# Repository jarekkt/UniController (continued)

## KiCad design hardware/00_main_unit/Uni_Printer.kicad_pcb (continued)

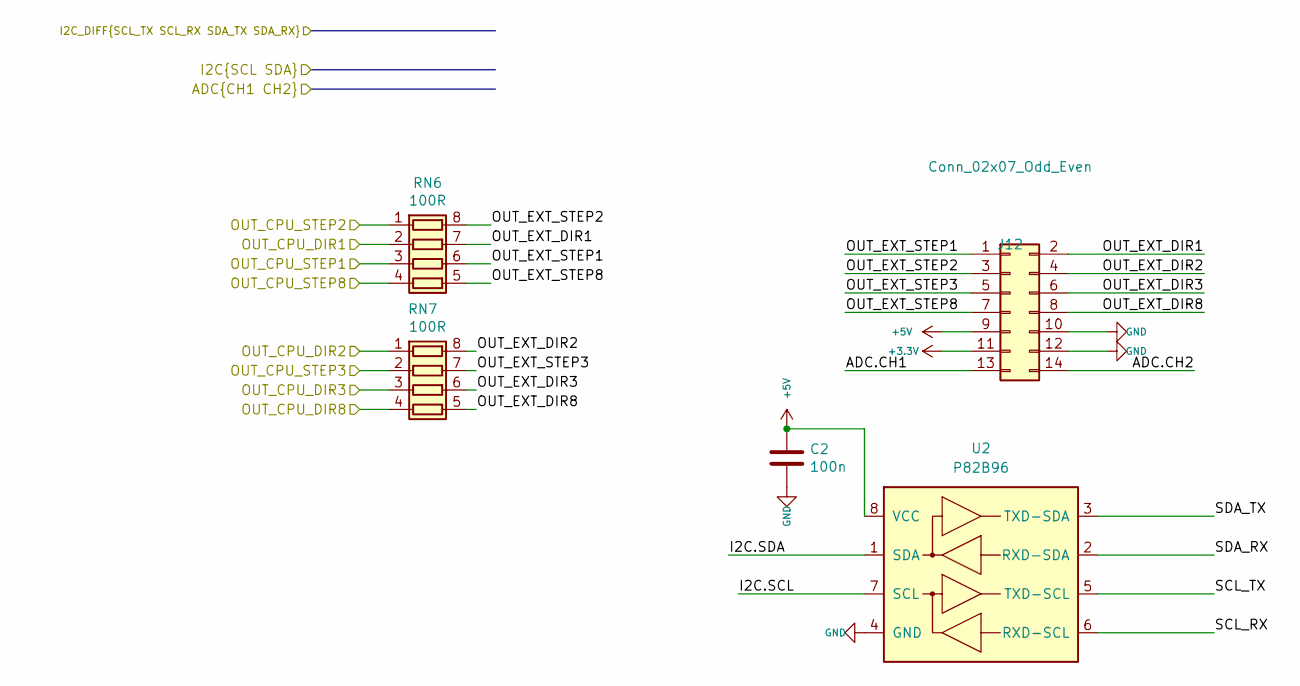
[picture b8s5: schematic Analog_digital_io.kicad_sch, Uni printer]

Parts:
C2: 100n; C_0603_1608Metric
J12: Conn_02x07_Odd_Even; PinHeader_2x07_P2.54mm_Vertical
RN6, RN7: 100R; R_Array_Convex_4x0603
U2: P82B96; TSSOP-8_4.4x3mm_P0.65mm

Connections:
+5V: C2.1, J12.9, U2.8 (VCC); also elsewhere on the board
/ADC.CH1: J12.13; also elsewhere on the board
/ADC.CH2: J12.14; also elsewhere on the board
/Analog Digital IO/OUT_EXT_DIR1: J12.2, RN6.7 (R2.2)
/Analog Digital IO/OUT_EXT_DIR2: J12.4, RN7.8 (R1.2)
/Analog Digital IO/OUT_EXT_DIR3: J12.6, RN7.6 (R3.2)
/Analog Digital IO/OUT_EXT_DIR8: J12.8, RN7.5 (R4.2)
/Analog Digital IO/OUT_EXT_STEP1: J12.1, RN6.6 (R3.2)
/Analog Digital IO/OUT_EXT_STEP2: J12.3, RN6.8 (R1.2)
/Analog Digital IO/OUT_EXT_STEP3: J12.5, RN7.7 (R2.2)
/Analog Digital IO/OUT_EXT_STEP8: J12.7, RN6.5 (R4.2)
/Analog Digital IO/SCL_RX: U2.6 (RXD-SCL)
/Analog Digital IO/SCL_TX: U2.5 (TXD-SCL)
/Analog Digital IO/SDA_RX: U2.2 (RXD-SDA)
/Analog Digital IO/SDA_TX: U2.3 (TXD-SDA)
/I2C.SCL: U2.7 (SCL); also elsewhere on the board
/I2C.SDA: U2.1 (SDA); also elsewhere on the board
/OUT_DIR1: RN6.2 (R2.1); also elsewhere on the board
/OUT_DIR2: RN7.1 (R1.1); also elsewhere on the board
/OUT_DIR3: RN7.3 (R3.1); also elsewhere on the board
/OUT_DIR8: RN7.4 (R4.1); also elsewhere on the board
/OUT_STEP1: RN6.3 (R3.1); also elsewhere on the board
/OUT_STEP2: RN6.1 (R1.1); also elsewhere on the board
/OUT_STEP3: RN7.2 (R2.1); also elsewhere on the board
/OUT_STEP8: RN6.4 (R4.1); also elsewhere on the board

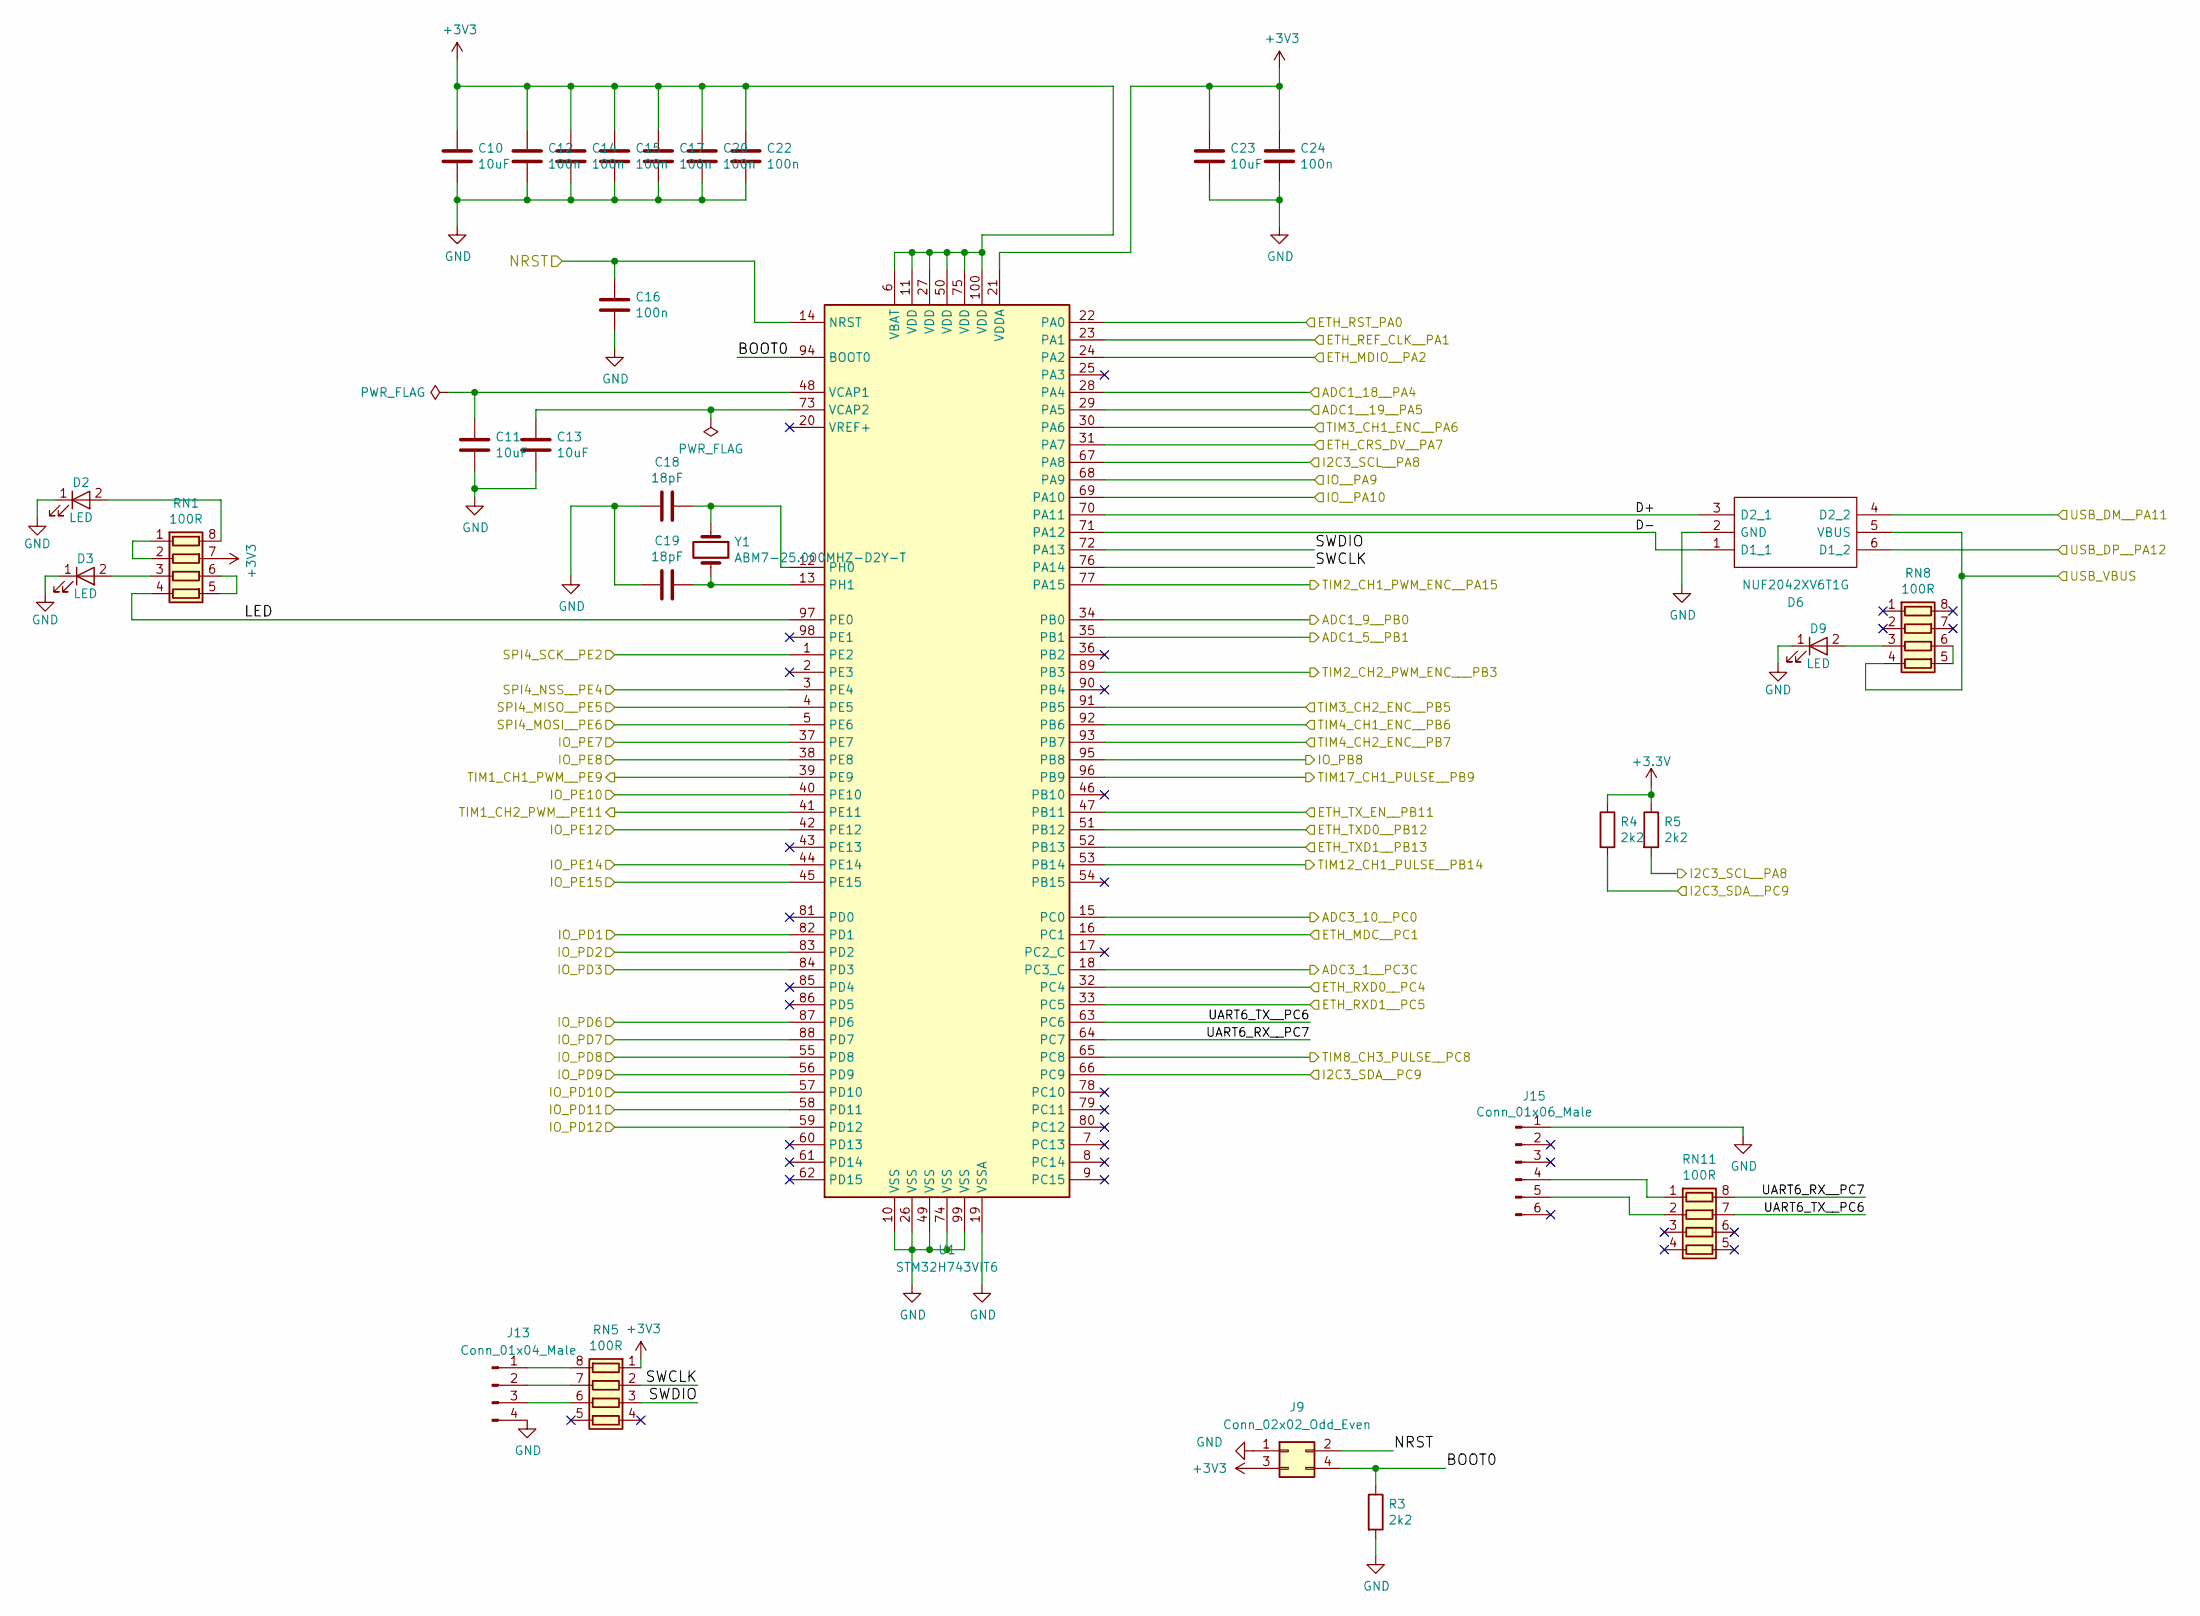
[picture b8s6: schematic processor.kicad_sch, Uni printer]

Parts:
C10, C11, C13, C23: 10uF; C_0603_1608Metric
C12, C14, C15, C16, C17, C20, C22, C24: 100n; C_0603_1608Metric
C18, C19: 18pF; C_0603_1608Metric
D2, D3, D9: LED; LED_0805_2012Metric
D6: NUF2042XV6T1G; SOT50P160X60-6N
J9: Conn_02x02_Odd_Even; PinHeader_2x02_P2.54mm_Vertical
J13: Conn_01x04_Male; PinHeader_1x04_P2.54mm_Vertical
J15: Conn_01x06_Male; PinHeader_1x06_P2.54mm_Vertical
R3, R4, R5: 2k2; R_0603_1608Metric
RN1, RN5, RN8, RN11: 100R; R_Array_Convex_4x0603
U1: STM32H743VIT6; LQFP-100_14x14mm_P0.5mm; Digi 497-17720-ND
Y1: ABM7-25.000MHZ-D2Y-T; XTAL500X320X130N_v2

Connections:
/ADC.CH1: U1.15 (PC0); also elsewhere on the board
/ADC.CH2: U1.18 (PC3_C); also elsewhere on the board
/AIN_IN_ADC5: U1.28 (PA4); also elsewhere on the board
/AIN_IN_ADC6: U1.29 (PA5); also elsewhere on the board
/AIN_IN_ADC7: U1.34 (PB0); also elsewhere on the board
/AIN_IN_ADC8: U1.35 (PB1); also elsewhere on the board
/ENC1.CH1: U1.30 (PA6); also elsewhere on the board
/ENC1.CH2: U1.91 (PB5); also elsewhere on the board
/ENC2.CH1: U1.92 (PB6); also elsewhere on the board
/ENC2.CH2: U1.93 (PB7); also elsewhere on the board
/ENC3.CH1: U1.77 (PA15); also elsewhere on the board
/ENC3.CH2: U1.89 (PB3); also elsewhere on the board
/Ethernet/ENET_CRSDV: U1.31 (PA7); also elsewhere on the board
/Ethernet/ENET_MDC: U1.16 (PC1); also elsewhere on the board
/Ethernet/ENET_MDIO: U1.24 (PA2); also elsewhere on the board
/Ethernet/ENET_REF_CLK: U1.23 (PA1); also elsewhere on the board
/Ethernet/ENET_RST: U1.22 (PA0); also elsewhere on the board
/Ethernet/ENET_RXD0: U1.32 (PC4); also elsewhere on the board
/Ethernet/ENET_RXD1: U1.33 (PC5); also elsewhere on the board
/Ethernet/ENET_TXD0: U1.51 (PB12); also elsewhere on the board
/Ethernet/ENET_TXD1: U1.52 (PB13); also elsewhere on the board
/Ethernet/ENET_TX_EN: U1.47 (PB11); also elsewhere on the board
/I2C.SCL: R5.2, U1.67 (PA8); also elsewhere on the board
/I2C.SDA: R4.2, U1.66 (PC9); also elsewhere on the board
/IN_CPU1: U1.37 (PE7); also elsewhere on the board
/IN_CPU2: U1.38 (PE8)
/IN_CPU3: U1.40 (PE10); also elsewhere on the board
/IN_CPU4: U1.42 (PE12); also elsewhere on the board
/IN_CPU9: U1.45 (PE15)
/IN_CPU10: U1.44 (PE14)
/OUT_CPU1: U1.84 (PD3); also elsewhere on the board
/OUT_CPU2: U1.58 (PD11); also elsewhere on the board
/OUT_CPU3: U1.57 (PD10); also elsewhere on the board
/OUT_CPU4: U1.56 (PD9); also elsewhere on the board
/OUT_CPU5: U1.39 (PE9); also elsewhere on the board
/OUT_CPU6: U1.41 (PE11); also elsewhere on the board
/OUT_DIR1: U1.87 (PD6); also elsewhere on the board
/OUT_DIR2: U1.88 (PD7); also elsewhere on the board
/OUT_DIR3: U1.55 (PD8); also elsewhere on the board
/OUT_DIR4: U1.95 (PB8); also elsewhere on the board
/OUT_DIR5: U1.4 (PE5); also elsewhere on the board
/OUT_DIR6: U1.3 (PE4); also elsewhere on the board
/OUT_DIR7: U1.69 (PA10); also elsewhere on the board
/OUT_DIR8: U1.83 (PD2); also elsewhere on the board
/OUT_STEP1: U1.65 (PC8); also elsewhere on the board
/OUT_STEP2: U1.53 (PB14); also elsewhere on the board
/OUT_STEP3: U1.96 (PB9); also elsewhere on the board
/OUT_STEP4: U1.59 (PD12); also elsewhere on the board
/OUT_STEP5: U1.1 (PE2); also elsewhere on the board
/OUT_STEP6: U1.5 (PE6); also elsewhere on the board
/OUT_STEP7: U1.68 (PA9); also elsewhere on the board
/OUT_STEP8: U1.82 (PD1); also elsewhere on the board
/Processor/BOOT0: J9.4, R3.1, U1.94 (BOOT0)
/Processor/D+: D6.3 (D2_1), U1.70 (PA11)
/Processor/D-: D6.1 (D1_1), U1.71 (PA12)
/Processor/LED: RN1.4 (R4.1), U1.97 (PE0)
/Processor/NRST: C16.1, J9.2, U1.14 (NRST); also elsewhere on the board
/Processor/SWCLK: RN5.2 (R2.1), U1.76 (PA14)
/Processor/SWDIO: RN5.3 (R3.1), U1.72 (PA13)
/Processor/UART6_RX__PC7: RN11.8 (R1.2), U1.64 (PC7)
/Processor/UART6_TX__PC6: RN11.7 (R2.2), U1.63 (PC6)
/USB.D+: D6.6 (D1_2); also elsewhere on the board
/USB.D-: D6.4 (D2_2); also elsewhere on the board
/USB.VBUS: D6.5 (VBUS), RN8.4 (R4.1); also elsewhere on the board
unnamed: C11.1, U1.48 (VCAP1)
unnamed: C13.1, U1.73 (VCAP2)
unnamed: C18.1, U1.12 (PH0), Y1.1
unnamed: C19.1, U1.13 (PH1), Y1.2
unnamed: D2.2 (A), RN1.8 (R1.2)
unnamed: D3.2 (A), RN1.3 (R3.1)
unnamed: D9.2 (A), RN8.3 (R3.1)
unnamed: J13.1, RN5.8 (R1.2)
unnamed: J13.2, RN5.7 (R2.2)
unnamed: J13.3, RN5.6 (R3.2)
unnamed: J15.4, RN11.1 (R1.1)
unnamed: J15.5, RN11.2 (R2.1)
unnamed: RN1.1 (R1.1), RN1.2 (R2.1)
unnamed: RN1.5 (R4.2), RN1.6 (R3.2)
unnamed: RN8.5 (R4.2), RN8.6 (R3.2)

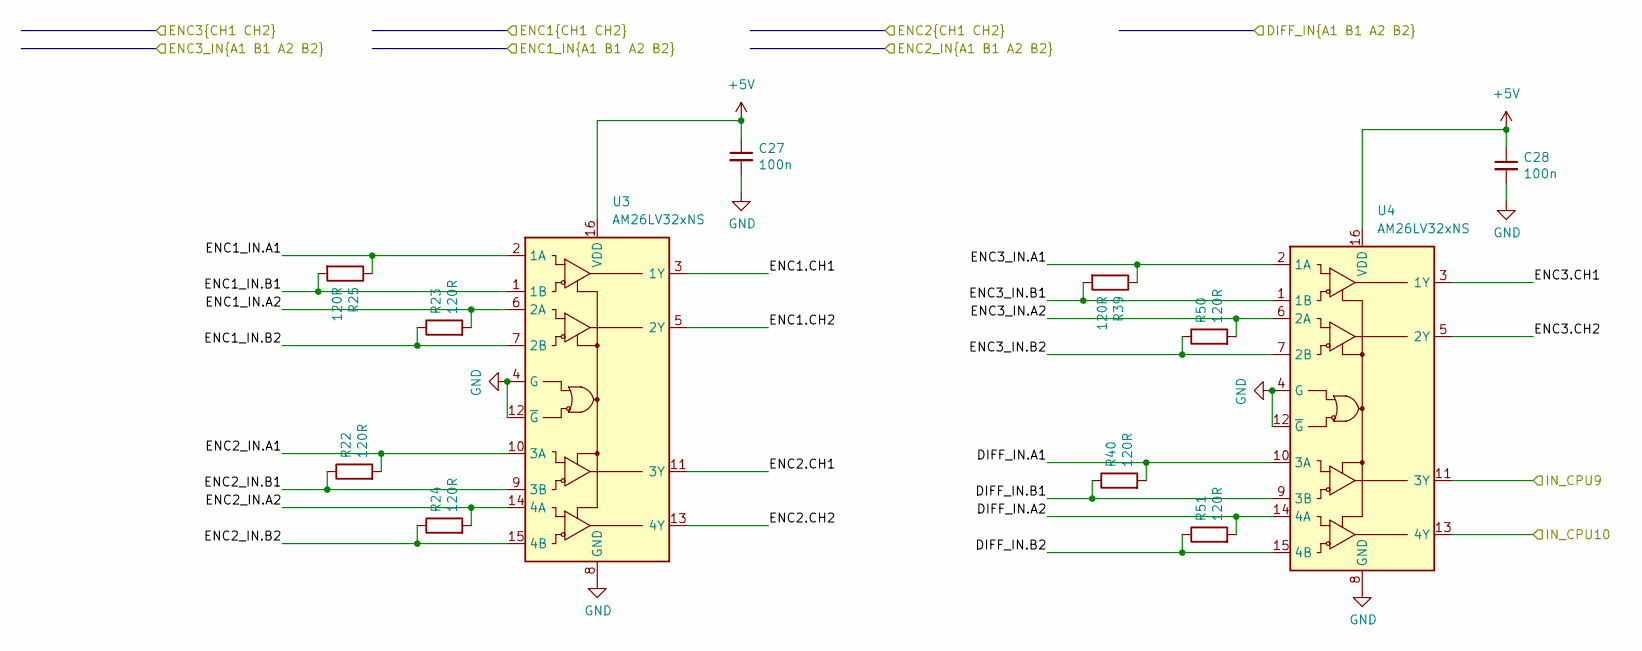
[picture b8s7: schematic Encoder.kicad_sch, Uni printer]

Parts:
C27, C28: 100n; C_0603_1608Metric
R22, R23, R24, R25, R39, R40, R50, R51: 120R; R_0603_1608Metric
U3, U4: AM26LV32xNS; SOIC-16W_5.3x10.2mm_P1.27mm

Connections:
+5V: C27.1, C28.1, U3.16 (VDD), U4.16 (VDD); also elsewhere on the board
/Connectors/DIFF_IN.A1: R40.2, U4.10 (3A); also elsewhere on the board
/Connectors/DIFF_IN.A2: R51.2, U4.14 (4A); also elsewhere on the board
/Connectors/DIFF_IN.B1: R40.1, U4.9 (3B); also elsewhere on the board
/Connectors/DIFF_IN.B2: R51.1, U4.15 (4B); also elsewhere on the board
/Connectors/ENC1_IN.A1: R25.1, U3.2 (1A); also elsewhere on the board
/Connectors/ENC1_IN.A2: R23.2, U3.6 (2A); also elsewhere on the board
/Connectors/ENC1_IN.B1: R25.2, U3.1 (1B); also elsewhere on the board
/Connectors/ENC1_IN.B2: R23.1, U3.7 (2B); also elsewhere on the board
/Connectors/ENC2_IN.A1: R22.2, U3.10 (3A); also elsewhere on the board
/Connectors/ENC2_IN.A2: R24.2, U3.14 (4A); also elsewhere on the board
/Connectors/ENC2_IN.B1: R22.1, U3.9 (3B); also elsewhere on the board
/Connectors/ENC2_IN.B2: R24.1, U3.15 (4B); also elsewhere on the board
/Connectors/ENC3_IN.A1: R39.1, U4.2 (1A); also elsewhere on the board
/Connectors/ENC3_IN.A2: R50.2, U4.6 (2A); also elsewhere on the board
/Connectors/ENC3_IN.B1: R39.2, U4.1 (1B); also elsewhere on the board
/Connectors/ENC3_IN.B2: R50.1, U4.7 (2B); also elsewhere on the board
/ENC1.CH1: U3.3 (1Y); also elsewhere on the board
/ENC1.CH2: U3.5 (2Y); also elsewhere on the board
/ENC2.CH1: U3.11 (3Y); also elsewhere on the board
/ENC2.CH2: U3.13 (4Y); also elsewhere on the board
/ENC3.CH1: U4.3 (1Y); also elsewhere on the board
/ENC3.CH2: U4.5 (2Y); also elsewhere on the board
/Encoder/IN_CPU9: U4.11 (3Y)
/Encoder/IN_CPU10: U4.13 (4Y)

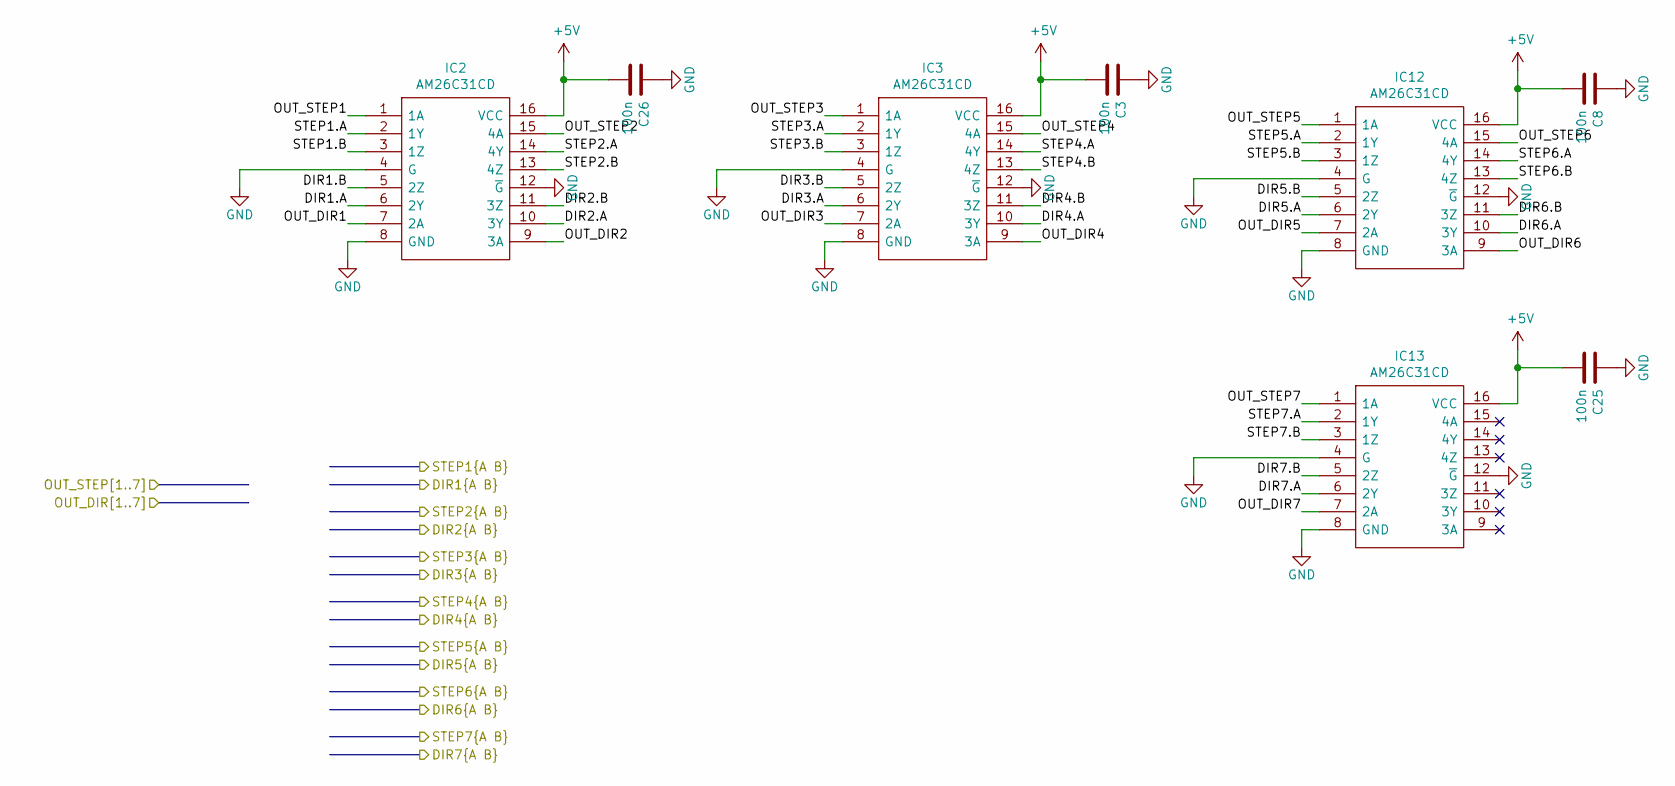
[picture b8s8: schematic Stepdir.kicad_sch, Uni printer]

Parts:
C3, C8, C25, C26: 100n; C_0603_1608Metric
IC2, IC3, IC12, IC13: AM26C31CD; SOIC127P600X175-16N; Manufacturer_Part_Number AM26C31CD; Mouser Part Number 595-AM26C31CD

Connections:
+5V: C3.2, C8.2, C25.2, C26.2, IC2.16 (VCC), IC3.16 (VCC), IC12.16 (VCC), IC13.16 (VCC); also elsewhere on the board
/Connectors/DIR1.A: IC2.6 (2Y); also elsewhere on the board
/Connectors/DIR1.B: IC2.5 (2Z); also elsewhere on the board
/Connectors/DIR2.A: IC2.10 (3Y); also elsewhere on the board
/Connectors/DIR2.B: IC2.11 (3Z); also elsewhere on the board
/Connectors/DIR3.A: IC3.6 (2Y); also elsewhere on the board
/Connectors/DIR3.B: IC3.5 (2Z); also elsewhere on the board
/Connectors/DIR4.A: IC3.10 (3Y); also elsewhere on the board
/Connectors/DIR4.B: IC3.11 (3Z); also elsewhere on the board
/Connectors/DIR5.A: IC12.6 (2Y); also elsewhere on the board
/Connectors/DIR5.B: IC12.5 (2Z); also elsewhere on the board
/Connectors/DIR6.A: IC12.14 (4Y); also elsewhere on the board
/Connectors/DIR6.B: IC12.13 (4Z); also elsewhere on the board
/Connectors/DIR7.A: IC13.6 (2Y); also elsewhere on the board
/Connectors/DIR7.B: IC13.5 (2Z); also elsewhere on the board
/Connectors/STEP1.A: IC2.2 (1Y); also elsewhere on the board
/Connectors/STEP1.B: IC2.3 (1Z); also elsewhere on the board
/Connectors/STEP2.A: IC2.14 (4Y); also elsewhere on the board
/Connectors/STEP2.B: IC2.13 (4Z); also elsewhere on the board
/Connectors/STEP3.A: IC3.2 (1Y); also elsewhere on the board
/Connectors/STEP3.B: IC3.3 (1Z); also elsewhere on the board
/Connectors/STEP4.A: IC3.14 (4Y); also elsewhere on the board
/Connectors/STEP4.B: IC3.13 (4Z); also elsewhere on the board
/Connectors/STEP5.A: IC12.2 (1Y); also elsewhere on the board
/Connectors/STEP5.B: IC12.3 (1Z); also elsewhere on the board
/Connectors/STEP6.A: IC12.10 (3Y); also elsewhere on the board
/Connectors/STEP6.B: IC12.11 (3Z); also elsewhere on the board
/Connectors/STEP7.A: IC13.2 (1Y); also elsewhere on the board
/Connectors/STEP7.B: IC13.3 (1Z); also elsewhere on the board
/OUT_DIR1: IC2.7 (2A); also elsewhere on the board
/OUT_DIR2: IC2.9 (3A); also elsewhere on the board
/OUT_DIR3: IC3.7 (2A); also elsewhere on the board
/OUT_DIR4: IC3.9 (3A); also elsewhere on the board
/OUT_DIR5: IC12.7 (2A); also elsewhere on the board
/OUT_DIR6: IC12.9 (3A); also elsewhere on the board
/OUT_DIR7: IC13.7 (2A); also elsewhere on the board
/OUT_STEP1: IC2.1 (1A); also elsewhere on the board
/OUT_STEP2: IC2.15 (4A); also elsewhere on the board
/OUT_STEP3: IC3.1 (1A); also elsewhere on the board
/OUT_STEP4: IC3.15 (4A); also elsewhere on the board
/OUT_STEP5: IC12.1 (1A); also elsewhere on the board
/OUT_STEP6: IC12.15 (4A); also elsewhere on the board
/OUT_STEP7: IC13.1 (1A); also elsewhere on the board

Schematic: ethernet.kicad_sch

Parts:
C4, C5, C6, C7: 18pF; C_0603_1608Metric
C9: 10uF; C_0603_1608Metric
C21, C33, C35, C36, C37: 100n; C_0603_1608Metric
CP1: 2.2uF; C_0603_1608Metric
CP2: 470pF; C_0603_1608Metric
IC5: LAN8742A; QFN-24-1EP_4x4mm_P0.5mm_EP2.6x2.6mm
J11: LMJ1998824110DL1T39J
L1: 10nH; L_0603_1608Metric
R1: 33; R_0603_1608Metric
R2, R38: 12k1; R_0603_1608Metric
R45, R46, R47, R48: 49R9; R_0603_1608Metric
RN2: 10k; R_Array_Convex_4x0603
RN3, RN10: 390R; R_Array_Convex_4x0603
Y2: ABM7-25.000MHZ-D2Y-T; XTAL500X320X130N_v2

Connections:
/Ethernet/ENET_CRSDV: IC5.11 (CRS_DV/MODE2); also elsewhere on the board
/Ethernet/ENET_MDC: C7.1, IC5.13 (MDC); also elsewhere on the board
/Ethernet/ENET_MDIO: C6.1, IC5.12 (MDIO), RN3.1 (R1.1); also elsewhere on the board
/Ethernet/ENET_REF_CLK: R1.1; also elsewhere on the board
/Ethernet/ENET_RST: IC5.15 (RST), RN2.7 (R2.2), RN2.8 (R1.2); also elsewhere on the board
/Ethernet/ENET_RXD0: IC5.8 (RXD0/MODE0); also elsewhere on the board
/Ethernet/ENET_RXD1: IC5.7 (RXD1/MODE1); also elsewhere on the board
/Ethernet/ENET_TXD0: IC5.17 (TXD0); also elsewhere on the board
/Ethernet/ENET_TXD1: IC5.18 (TXD1); also elsewhere on the board
/Ethernet/ENET_TX_EN: IC5.16 (TXEN); also elsewhere on the board
/Ethernet/RJ45_LED1: J11.9 (LEDG_A), RN10.7 (R2.2), RN10.8 (R1.2)
/Ethernet/RJ45_LED2: J11.11 (LEDY_A), RN10.5 (R4.2), RN10.6 (R3.2)
/Ethernet/RX+: IC5.23 (RXP), J11.4 (RD+), R47.1
/Ethernet/RX-: IC5.22 (RXN), J11.6 (RD-), R48.1
/Ethernet/TX+: IC5.21 (TXP), J11.1 (TD+), R45.1
/Ethernet/TX-: IC5.20 (TXN), J11.3 (TD-), R46.1
/Ethernet/VDD: C9.1, C21.2, C33.2, C35.2, C36.1, C37.1, IC5.1 (VDD2A), IC5.9 (VDDIO), IC5.19 (VDD1A), J11.2 (TCT), J11.5 (RCT), L1.1, R45.2, R46.2, R47.2, R48.2, RN2.1 (R1.1), RN2.2 (R2.1), RN2.3 (R3.1), RN2.4 (R4.1), RN3.4 (R4.1)
/Ethernet/VDDCR: CP1.1, CP2.1, IC5.6 (VDDCR)
unnamed: C4.1, IC5.5 (XTAL1/CLKIN), Y2.1
unnamed: C5.1, IC5.4 (XTAL2), Y2.2
unnamed: IC5.2 (LED2/nINTSEL), R2.1, RN10.3 (R3.1), RN10.4 (R4.1)
unnamed: IC5.3 (LED1/REGOFF), RN10.1 (R1.1), RN10.2 (R2.1)
unnamed: IC5.14 (INT/REFCLKO), R1.2, RN2.5 (R4.2), RN2.6 (R3.2)
unnamed: IC5.24 (RBIAS), R38.1
unnamed: RN3.2 (R2.1), RN3.3 (R3.1)
unnamed: RN3.5 (R4.2), RN3.6 (R3.2)
unnamed: RN3.7 (R2.2), RN3.8 (R1.2)

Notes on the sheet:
VDDIO VDD1A VDD2A

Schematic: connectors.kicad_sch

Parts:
J1, J2, J3, J4, J7, J8, J14: Conn_01x10; PhoenixContact_MC-G_10x3.50mm_Angled
J10: USB B connector; USB_B_OST_USB-B1HSxx_Horizontal
J16, J17, J18: RJ45_Shielded; RJ45_Ninigi_GE
R49: 0R; R_0603_1608Metric

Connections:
+5V: J7.1, J8.1, J14.1; also elsewhere on the board
/Analog Digital IO/I2C_DIFF.SCL_RX: J16.7
/Analog Digital IO/I2C_DIFF.SCL_TX: J16.8
/Analog Digital IO/I2C_DIFF.SDA_TX: J16.6
/Connectors/AIN_IN5: J4.4; also elsewhere on the board
/Connectors/AIN_IN6: J4.7; also elsewhere on the board
/Connectors/AIN_IN7: J4.10; also elsewhere on the board
/Connectors/AIN_IN8: J3.3; also elsewhere on the board
/Connectors/AIN_IN_SUP5: J4.5; also elsewhere on the board
/Connectors/AIN_IN_SUP6: J4.8; also elsewhere on the board
/Connectors/AIN_IN_SUP7: J3.1; also elsewhere on the board
/Connectors/AIN_IN_SUP8: J3.4; also elsewhere on the board
/Connectors/DIFF_IN.A1: J16.5; also elsewhere on the board
/Connectors/DIFF_IN.A2: J16.2; also elsewhere on the board
/Connectors/DIFF_IN.B1: J16.4; also elsewhere on the board
/Connectors/DIFF_IN.B2: J16.1; also elsewhere on the board
/Connectors/DIR1.A: J7.9; also elsewhere on the board
/Connectors/DIR1.B: J7.10; also elsewhere on the board
/Connectors/DIR2.A: J8.9; also elsewhere on the board
/Connectors/DIR2.B: J8.10; also elsewhere on the board
/Connectors/DIR3.A: J14.9; also elsewhere on the board
/Connectors/DIR3.B: J14.10; also elsewhere on the board
/Connectors/DIR4.A: J17.7; also elsewhere on the board
/Connectors/DIR4.B: J17.8; also elsewhere on the board
/Connectors/DIR5.A: J17.4; also elsewhere on the board
/Connectors/DIR5.B: J17.5; also elsewhere on the board
/Connectors/DIR6.A: J18.7; also elsewhere on the board
/Connectors/DIR6.B: J18.8; also elsewhere on the board
/Connectors/DIR7.A: J18.4; also elsewhere on the board
/Connectors/DIR7.B: J18.5; also elsewhere on the board
/Connectors/ENC1_IN.A1: J7.2; also elsewhere on the board
/Connectors/ENC1_IN.A2: J7.4; also elsewhere on the board
/Connectors/ENC1_IN.B1: J7.3; also elsewhere on the board
/Connectors/ENC1_IN.B2: J7.5; also elsewhere on the board
/Connectors/ENC2_IN.A1: J8.2; also elsewhere on the board
/Connectors/ENC2_IN.A2: J8.4; also elsewhere on the board
/Connectors/ENC2_IN.B1: J8.3; also elsewhere on the board
/Connectors/ENC2_IN.B2: J8.5; also elsewhere on the board
/Connectors/ENC3_IN.A1: J14.2; also elsewhere on the board
/Connectors/ENC3_IN.A2: J14.4; also elsewhere on the board
/Connectors/ENC3_IN.B1: J14.3; also elsewhere on the board
/Connectors/ENC3_IN.B2: J14.5; also elsewhere on the board
/Connectors/I2C_DIFF_SDA_RX: J16.3
/Connectors/IN1: J1.2; also elsewhere on the board
/Connectors/IN2: J1.5; also elsewhere on the board
/Connectors/IN3: J1.8; also elsewhere on the board
/Connectors/IN4: J4.1; also elsewhere on the board
/Connectors/IN_SUP1: J1.3; also elsewhere on the board
/Connectors/IN_SUP2: J1.6; also elsewhere on the board
/Connectors/IN_SUP3: J1.9; also elsewhere on the board
/Connectors/IN_SUP4: J4.2; also elsewhere on the board
/Connectors/OUT_HSW1: J3.6; also elsewhere on the board
/Connectors/OUT_HSW2: J3.8; also elsewhere on the board
/Connectors/OUT_HSW3: J3.10; also elsewhere on the board
/Connectors/OUT_HSW4: J2.2; also elsewhere on the board
/Connectors/OUT_HSW5: J2.4; also elsewhere on the board
/Connectors/OUT_HSW6: J2.6; also elsewhere on the board
/Connectors/STEP1.A: J7.7; also elsewhere on the board
/Connectors/STEP1.B: J7.8; also elsewhere on the board
/Connectors/STEP2.A: J8.7; also elsewhere on the board
/Connectors/STEP2.B: J8.8; also elsewhere on the board
/Connectors/STEP3.A: J14.7; also elsewhere on the board
/Connectors/STEP3.B: J14.8; also elsewhere on the board
/Connectors/STEP4.A: J17.3; also elsewhere on the board
/Connectors/STEP4.B: J17.6; also elsewhere on the board
/Connectors/STEP5.A: J17.1; also elsewhere on the board
/Connectors/STEP5.B: J17.2; also elsewhere on the board
/Connectors/STEP6.A: J18.3; also elsewhere on the board
/Connectors/STEP6.B: J18.6; also elsewhere on the board
/Connectors/STEP7.A: J18.1; also elsewhere on the board
/Connectors/STEP7.B: J18.2; also elsewhere on the board
/Connectors/SUPPY+: J2.9, J2.10; also elsewhere on the board
/USB.D+: J10.3 (D+); also elsewhere on the board
/USB.D-: J10.2 (D-); also elsewhere on the board
/USB.VBUS: J10.1 (VBUS); also elsewhere on the board
unnamed: J10.5 (Shield), R49.1

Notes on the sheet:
Inputs
Differential control and encoders
Communication
Outputs

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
